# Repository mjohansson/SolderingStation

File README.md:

# SolderingStation
Project directory for soldering-station 2000

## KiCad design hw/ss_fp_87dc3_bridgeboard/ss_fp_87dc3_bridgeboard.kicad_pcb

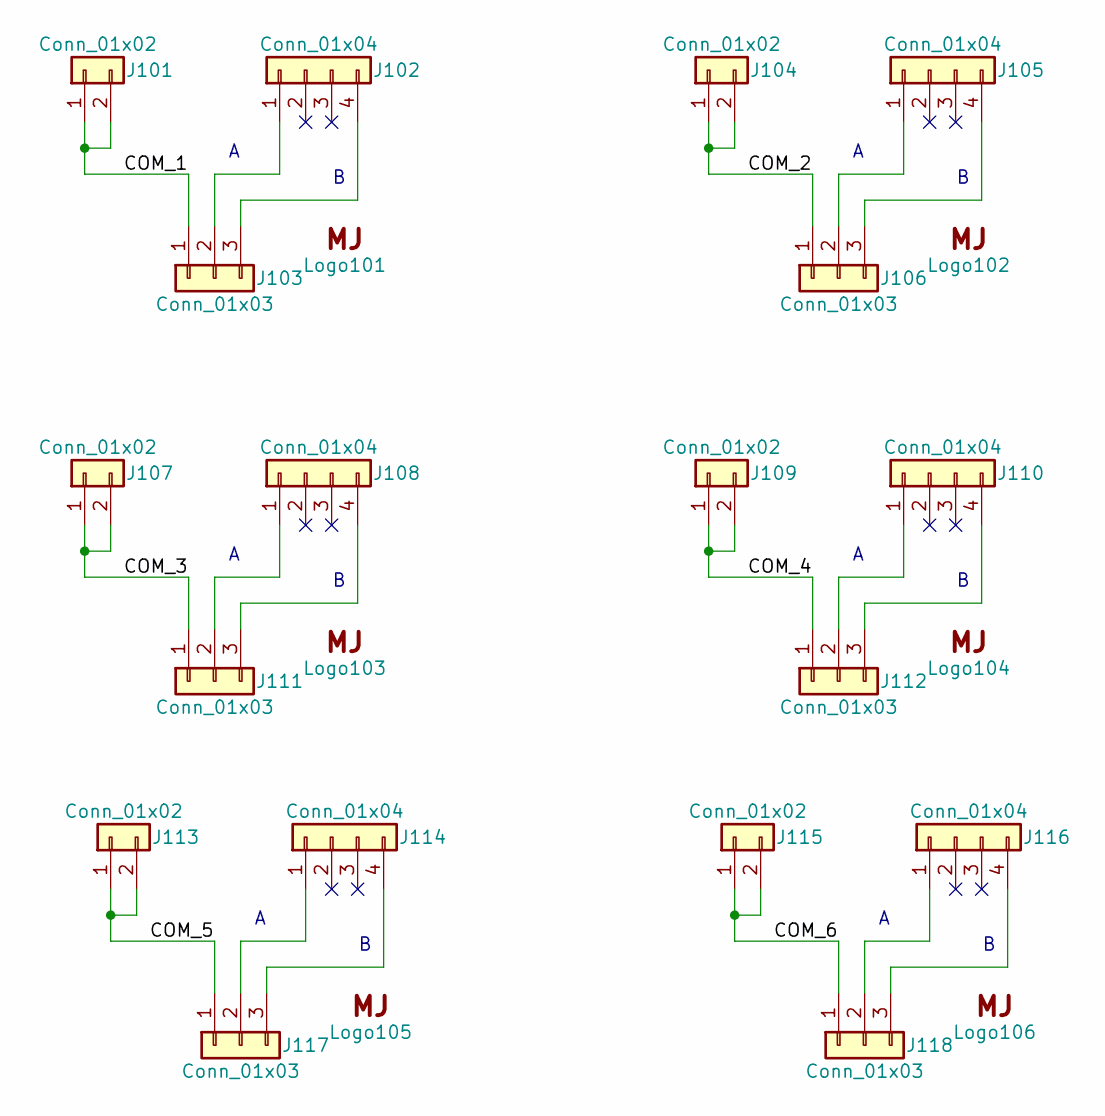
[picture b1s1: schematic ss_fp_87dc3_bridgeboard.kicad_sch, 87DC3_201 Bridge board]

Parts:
J101, J104, J107, J109, J113, J115: Conn_01x02; PinSocket_1x02_P2.54mm_Vertical
J102, J105, J108, J110, J114, J116: Conn_01x04; PinSocket_1x04_P2.54mm_Vertical
J103, J106, J111, J112, J117, J118: Conn_01x03; PinSocket_1x03_P2.54mm_Vertical
Logo101, Logo102, Logo103, Logo104, Logo105, Logo106: Logo_MJ; MJ_Mini

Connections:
/COM_1: J101.1, J101.2, J103.1
/COM_2: J104.1, J104.2, J106.1
/COM_3: J107.1, J107.2, J111.1
/COM_4: J109.1, J109.2, J112.1
/COM_5: J113.1, J113.2, J117.1
/COM_6: J115.1, J115.2, J118.1
unnamed: J102.1, J103.2
unnamed: J102.4, J103.3
unnamed: J105.1, J106.2
unnamed: J105.4, J106.3
unnamed: J108.1, J111.2
unnamed: J108.4, J111.3
unnamed: J110.1, J112.2
unnamed: J110.4, J112.3
unnamed: J114.1, J117.2
unnamed: J114.4, J117.3
unnamed: J116.1, J118.2
unnamed: J116.4, J118.3

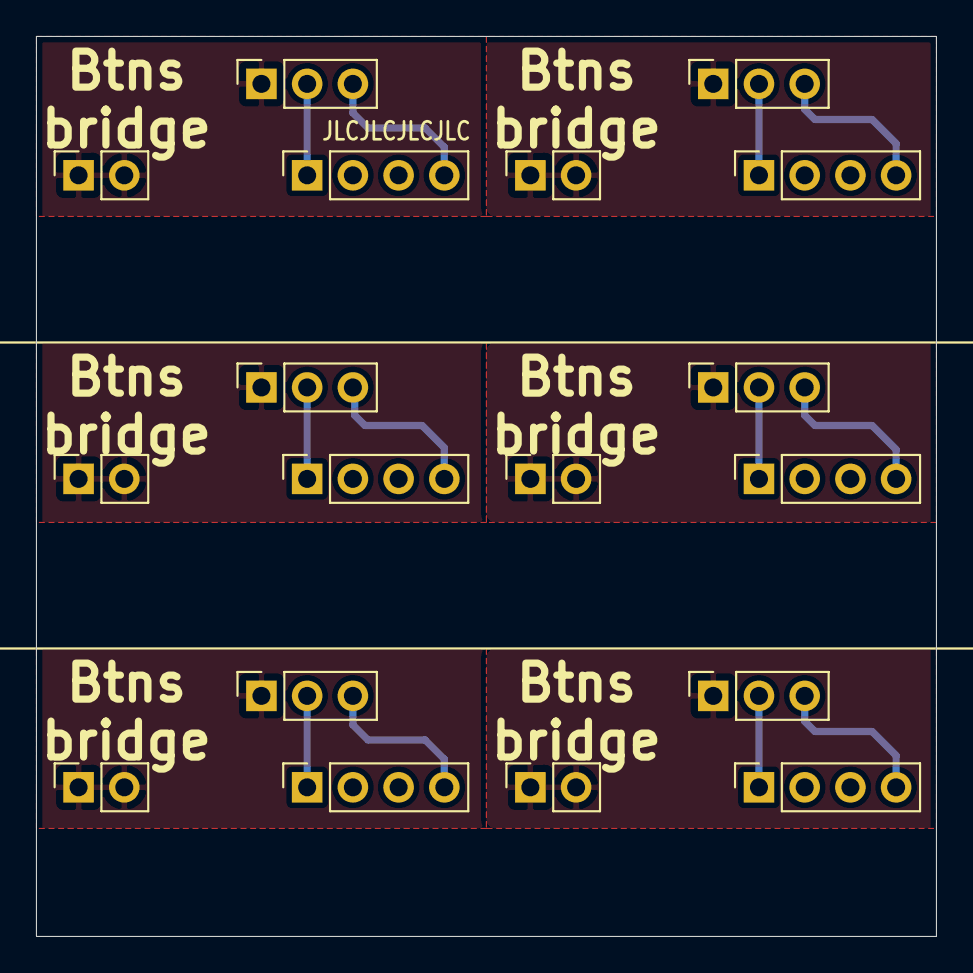
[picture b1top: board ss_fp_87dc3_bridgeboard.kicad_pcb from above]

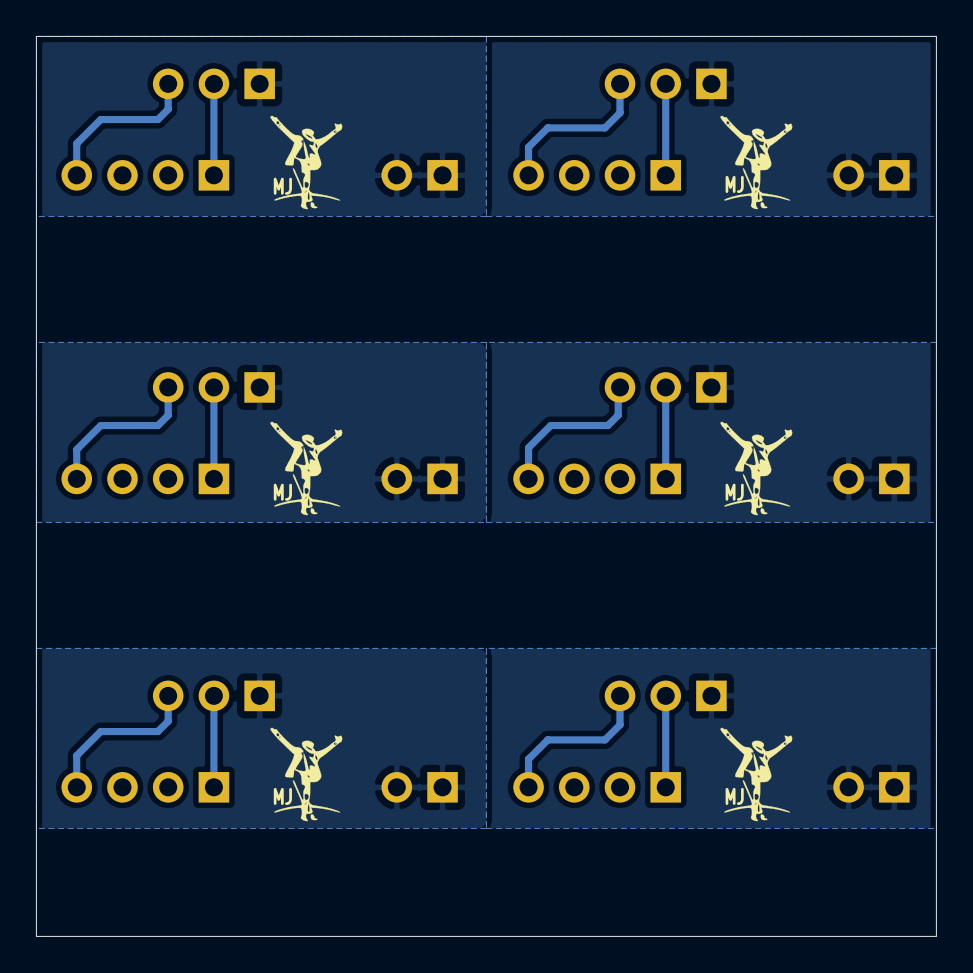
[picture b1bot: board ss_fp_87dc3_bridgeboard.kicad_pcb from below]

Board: 2 copper layers, 50.0 x 50.0 mm, 24 parts (6 on the bottom side), 18 nets.

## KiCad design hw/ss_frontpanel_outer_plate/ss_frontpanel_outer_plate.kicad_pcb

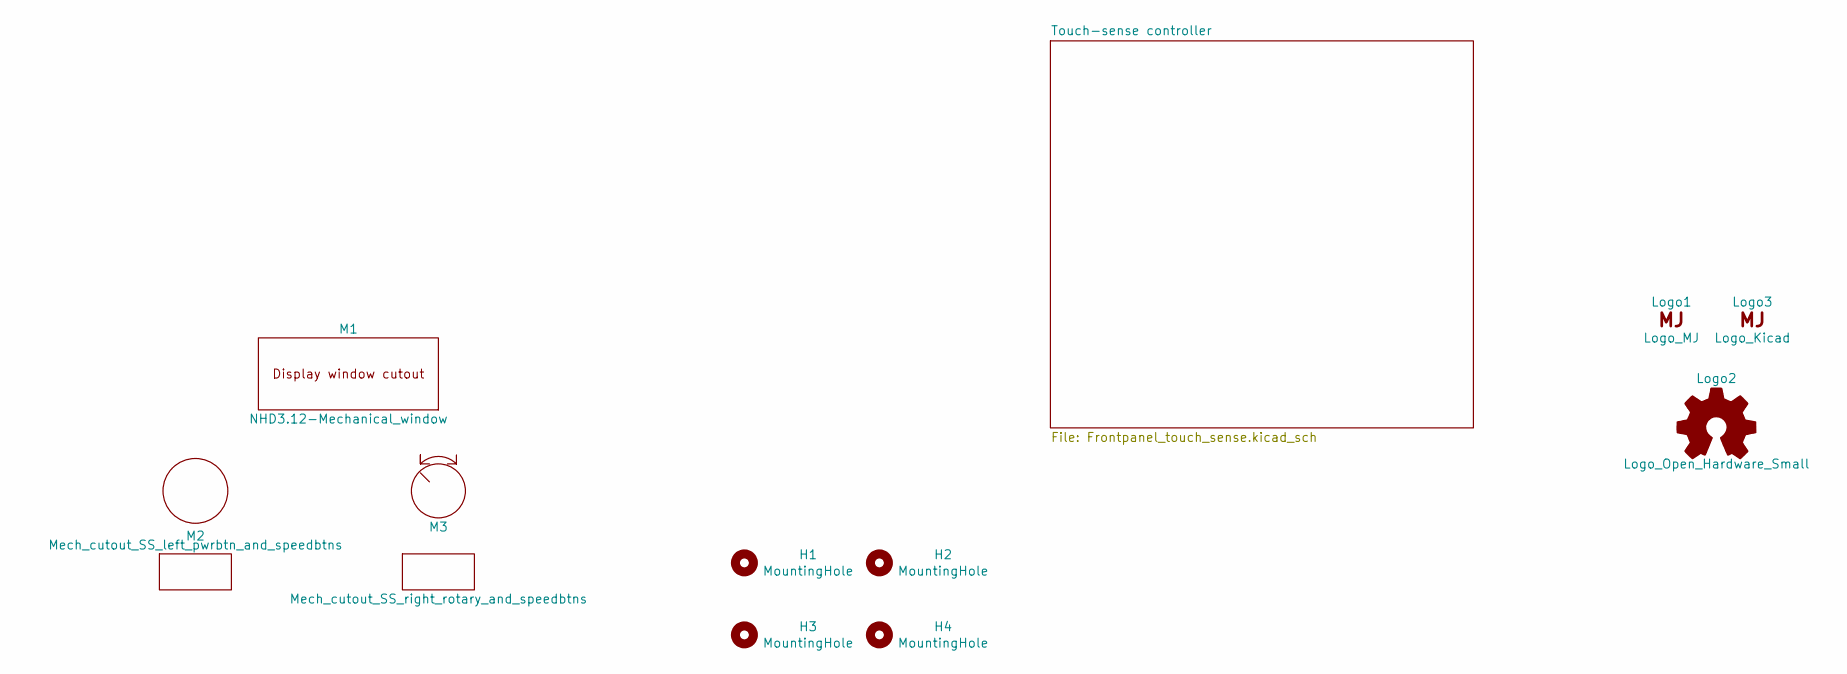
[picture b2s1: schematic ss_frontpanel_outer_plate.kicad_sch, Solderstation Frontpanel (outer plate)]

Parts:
H1, H2, H3, H4: MountingHole; MountingHole_3.5mm_Hammond_panel_screws
Logo1: Logo_MJ; MJ_10.3x12.7
Logo2: Logo_Open_Hardware_Small; OSHW-Logo_5.7x6mm_SilkScreen
Logo3: Logo_Kicad; KiCad-Logo2_5mm_SilkScreen
M1: NHD3.12-Mechanical_window; NHD3_12-Reverse_Bezel
M2: Mech_cutout_SS_left_pwrbtn_and_speedbtns; Frontpanel_L_Powerbtn_Pushbtns_outer_cutouts
M3: Mech_cutout_SS_right_rotary_and_speedbtns; Frontpanel_R_RotaryEnc_Pushbtns_outer_cutouts

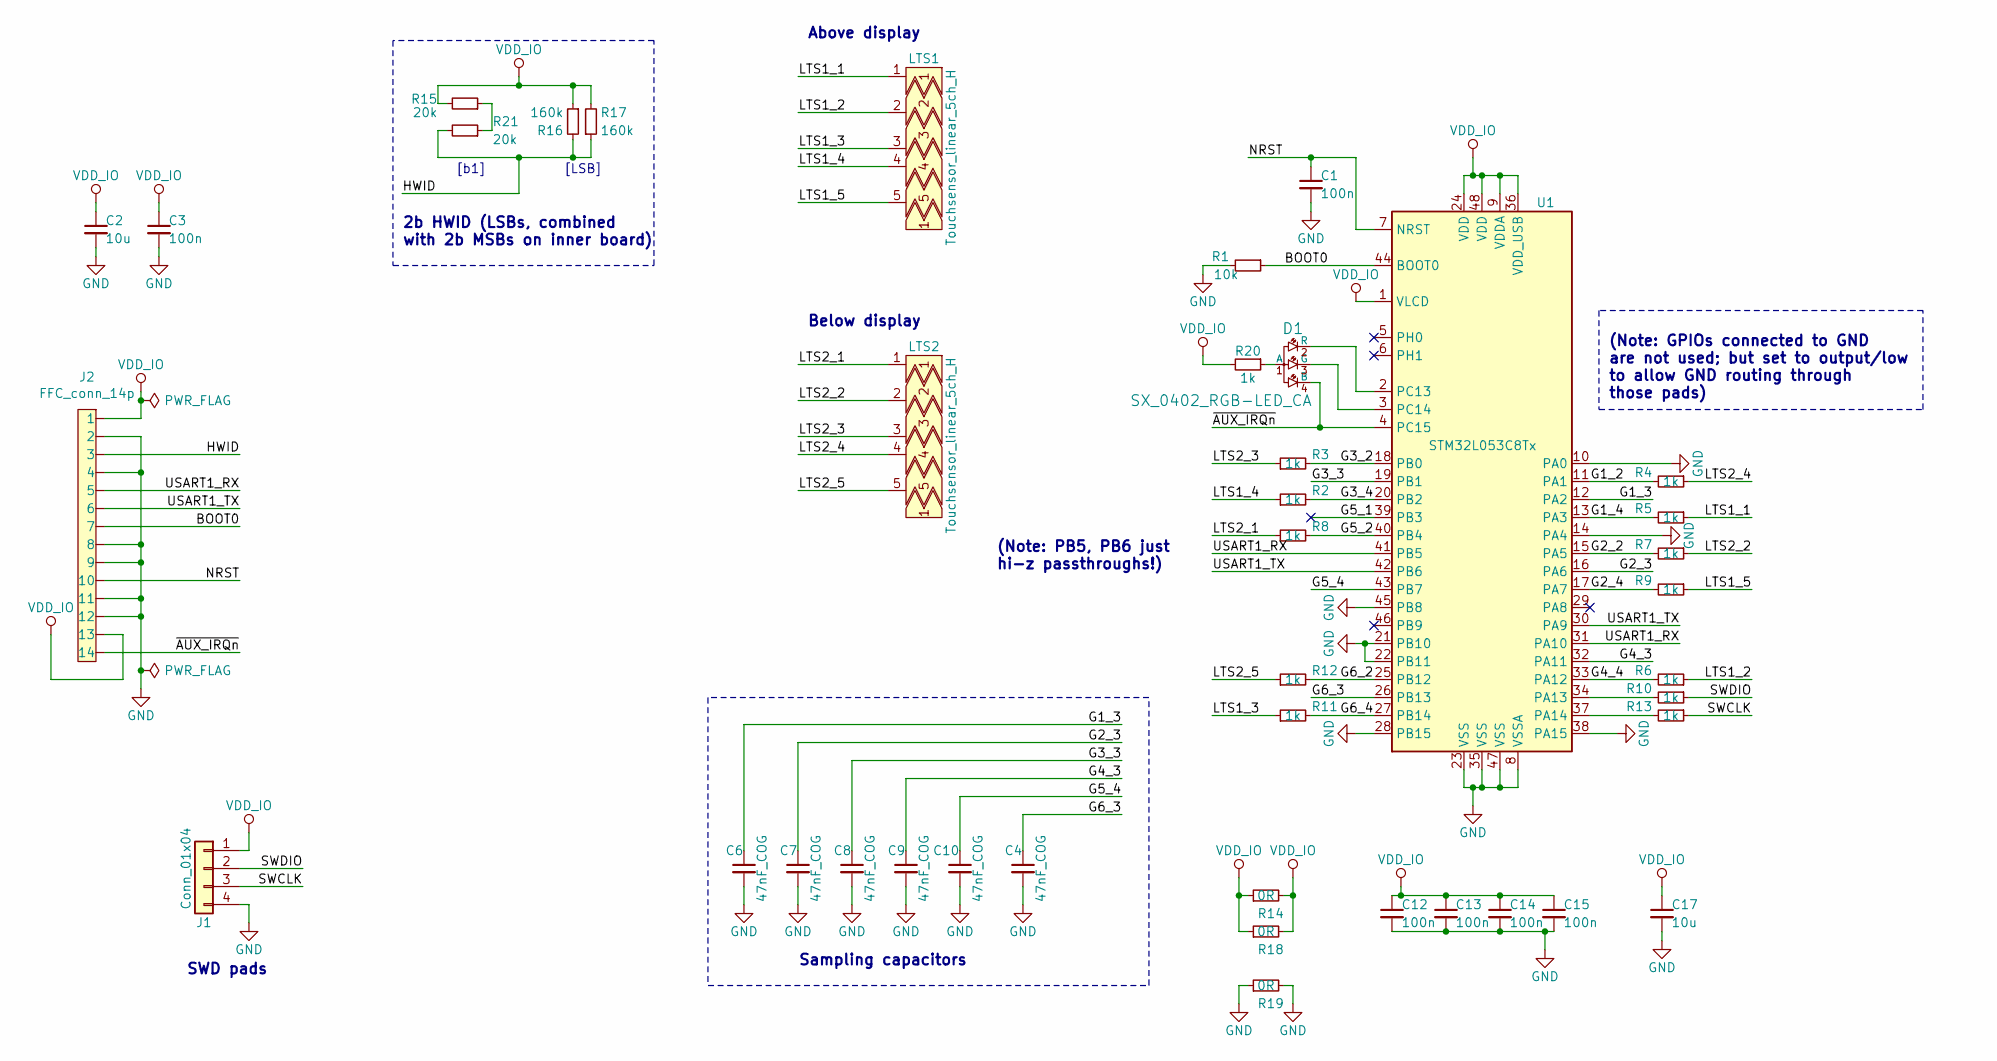
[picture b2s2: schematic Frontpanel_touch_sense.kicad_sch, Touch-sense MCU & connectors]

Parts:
C1, C3, C12, C13, C14, C15: 100n; C_0402_1005Metric
C2, C17: 10u; C_0402_1005Metric
C4, C6, C7, C8, C9, C10: 47nF_COG; C_1206_3216Metric
D1: SX_0402_RGB-LED_CA; SX_0402_RGB-CA-06
J1: Conn_01x04; 4pin_SWD_SMT_100mil
J2: FFC_conn_14p; FPC_14p_05mm-WE_687114182122
LTS1, LTS2: Touchsensor_linear_5ch_H; Touchsensor_linear_slider-5ch_H_90x8mm
R1: 10k; R_0402_1005Metric
R2, R3, R4, R5, R6, R7, R9, R10, R13, R20: 1k; R_0402_1005Metric
R8, R11: 1k; R_0603_1608Metric
R12: 1k; R_1206_3216Metric
R14, R18, R19: 0R; R_0603_1608Metric
R15, R21: 20k; R_0402_1005Metric
R16, R17: 160k; R_0402_1005Metric
U1: STM32L053C8Tx; LQFP-48_7x7mm_P0.5mm

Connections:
/Touch-sense controller/BOOT0: J2.7, R1.1, U1.44 (BOOT0)
/Touch-sense controller/G1_2: R4.2, U1.11 (PA1)
/Touch-sense controller/G1_3: C6.1, U1.12 (PA2)
/Touch-sense controller/G1_4: R5.2, U1.13 (PA3)
/Touch-sense controller/G2_2: R7.2, U1.15 (PA5)
/Touch-sense controller/G2_3: C7.1, U1.16 (PA6)
/Touch-sense controller/G2_4: R9.2, U1.17 (PA7)
/Touch-sense controller/G3_2: R3.2, U1.18 (PB0)
/Touch-sense controller/G3_3: C8.1, U1.19 (PB1)
/Touch-sense controller/G3_4: R2.2, U1.20 (PB2)
/Touch-sense controller/G4_3: C9.1, U1.32 (PA11)
/Touch-sense controller/G4_4: R6.2, U1.33 (PA12)
/Touch-sense controller/G5_1: U1.39 (PB3)
/Touch-sense controller/G5_2: R8.2, U1.40 (PB4)
/Touch-sense controller/G5_4: C10.1, U1.43 (PB7)
/Touch-sense controller/G6_2: R12.2, U1.25 (PB12)
/Touch-sense controller/G6_3: C4.1, U1.26 (PB13)
/Touch-sense controller/G6_4: R11.2, U1.27 (PB14)
/Touch-sense controller/HWID: J2.3, R16.2, R17.1, R21.2
/Touch-sense controller/LTS1_1: LTS1.1, R5.1
/Touch-sense controller/LTS1_2: LTS1.2, R6.1
/Touch-sense controller/LTS1_3: LTS1.3, R11.1
/Touch-sense controller/LTS1_4: LTS1.4, R2.1
/Touch-sense controller/LTS1_5: LTS1.5, R9.1
/Touch-sense controller/LTS2_1: LTS2.1, R8.1
/Touch-sense controller/LTS2_2: LTS2.2, R7.1
/Touch-sense controller/LTS2_3: LTS2.3, R3.1
/Touch-sense controller/LTS2_4: LTS2.4, R4.1
/Touch-sense controller/LTS2_5: LTS2.5, R12.1
/Touch-sense controller/NRST: C1.1, J2.10, U1.7 (NRST)
/Touch-sense controller/SWCLK: J1.3, R13.1
/Touch-sense controller/SWDIO: J1.2, R10.1
/Touch-sense controller/USART1_RX: J2.5, U1.31 (PA10), U1.41 (PB5)
/Touch-sense controller/USART1_TX: J2.6, U1.30 (PA9), U1.42 (PB6)
/Touch-sense controller/~AUX_IRQn: D1.4 (B), J2.14, U1.4 (PC15)
GND: C1.2, C2.2, C3.2, C4.2, C6.2, C7.2, C8.2, C9.2, C10.2, C12.2, C13.2, C14.2, C15.2, C17.2, J1.4, J2.2, J2.4, J2.8, J2.9, J2.11, J2.12, R1.2, R19.1, R19.2, U1.8 (VSSA), U1.10 (PA0), U1.14 (PA4), U1.21 (PB10), U1.22 (PB11), U1.23 (VSS), U1.28 (PB15), U1.35 (VSS), U1.38 (PA15), U1.45 (PB8), U1.47 (VSS)
unnamed: D1.1 (A), R20.1
unnamed: D1.2 (R), U1.2 (PC13)
unnamed: D1.3 (G), U1.3 (PC14)
unnamed: R10.2, U1.34 (PA13)
unnamed: R13.2, U1.37 (PA14)
unnamed: R15.1, R21.1
VDD_IO: C2.1, C3.1, C12.1, C13.1, C14.1, C15.1, C17.1, J1.1, J2.1, J2.13, R14.1, R14.2, R15.2, R16.1, R17.2, R18.1, R18.2, R20.2, U1.1 (VLCD), U1.9 (VDDA), U1.24 (VDD), U1.36 (VDD_USB), U1.48 (VDD)

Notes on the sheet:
(Note: PB5, PB6 just hi-z passthroughs!)
(Note: GPIOs connected to GND are not used; but set to output/low to allow GND routing through those pads)
SWD pads
[LSB]
Sampling capacitors
[b1]
Below display
2b HWID (LSBs, combined with 2b MSBs on inner board)
Above display

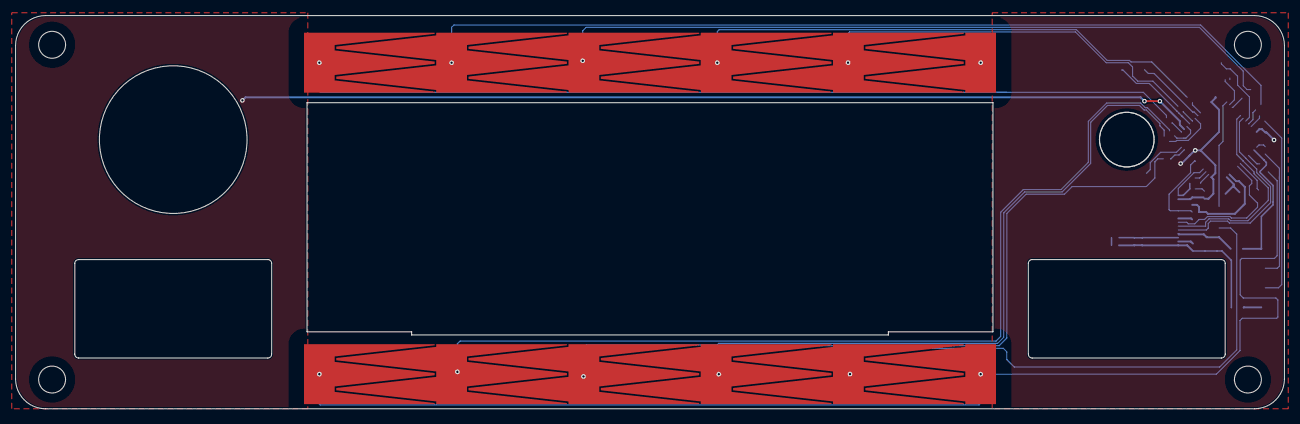
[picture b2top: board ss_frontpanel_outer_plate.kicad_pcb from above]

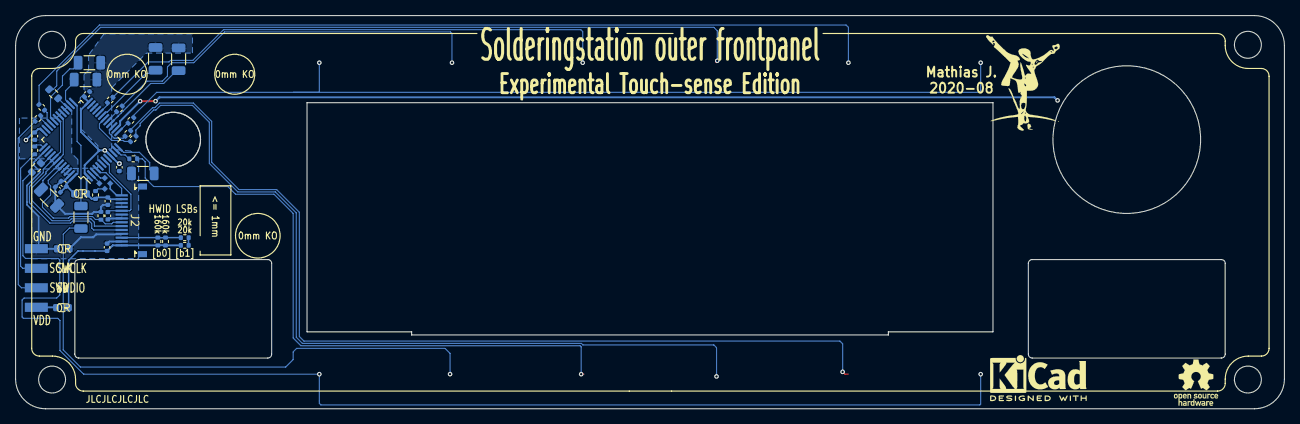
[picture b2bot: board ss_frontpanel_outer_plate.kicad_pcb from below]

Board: 2 copper layers, 165.0 x 51.1 mm, 51 parts (44 on the bottom side), 42 nets.

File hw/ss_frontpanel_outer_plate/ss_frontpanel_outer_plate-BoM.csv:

"Id";"Designator";"Package";"Quantity";"Designation";"Supplier and ref";
1;"H2,H3,H4,H1";"MountingHole_3.5mm_Hammond_panel_screws";4;"MountingHole";;;
2;"M1";"NHD3_12-Reverse_Bezel";1;"NHD3.12-Mechanical_window";;;
3;"LTS1,LTS2";"Touchsensor_linear_slider-5ch_H_90x8mm";2;"Touchsensor_linear_5ch_H";;;
4;"M2";"Frontpanel_L_Powerbtn_Pushbtns_outer_cutouts";1;"Mech_cutout_SS_left_pwrbtn_and_speedbtns";;;
5;"C1,C3,C12,C13,C15,C14";"C_0402_1005Metric";6;"100n";;;
6;"C6,C7,C8,C9,C4,C10";"C_1206_3216Metric";6;"47nF_COG";;;
7;"C17,C2";"C_0402_1005Metric";2;"10u";;;
8;"R1";"R_0402_1005Metric";1;"10k";;;
9;"R2,R6,R9,R5,R3,R4,R7,R10,R13,R20";"R_0402_1005Metric";10;"1k";;;
10;"R8,R11";"R_0603_1608Metric";2;"1k";;;
11;"R12";"R_1206_3216Metric";1;"1k";;;
12;"M3";"Frontpanel_R_RotaryEnc_Pushbtns_outer_cutouts";1;"Mech_cutout_SS_right_rotary_and_speedbtns";;;
13;"J2";"FPC_14p_05mm-WE_687114182122";1;"FFC_conn_14p";;;
14;"R17,R16";"R_0402_1005Metric";2;"160k";;;
15;"R18,R19,R14";"R_0603_1608Metric";3;"0R";;;
16;"J1";"4pin_SWD_SMT_100mil";1;"Conn_01x04";;;
17;"Logo1";"MJ_10.3x12.7";1;"Logo_MJ";;;
18;"Logo2";"OSHW-Logo_5.7x6mm_SilkScreen";1;"Logo_Open_Hardware_Small";;;
19;"Logo3";"KiCad-Logo2_5mm_SilkScreen";1;"Logo_Kicad";;;
20;"U1";"LQFP-48_7x7mm_P0.5mm";1;"STM32L052C8Tx";;;
21;"D1";"SX_0402_RGB-CA-06";1;"SX_0402_RGB-LED_CA";;;
22;"R15,R21";"R_0402_1005Metric";2;"20k";;;

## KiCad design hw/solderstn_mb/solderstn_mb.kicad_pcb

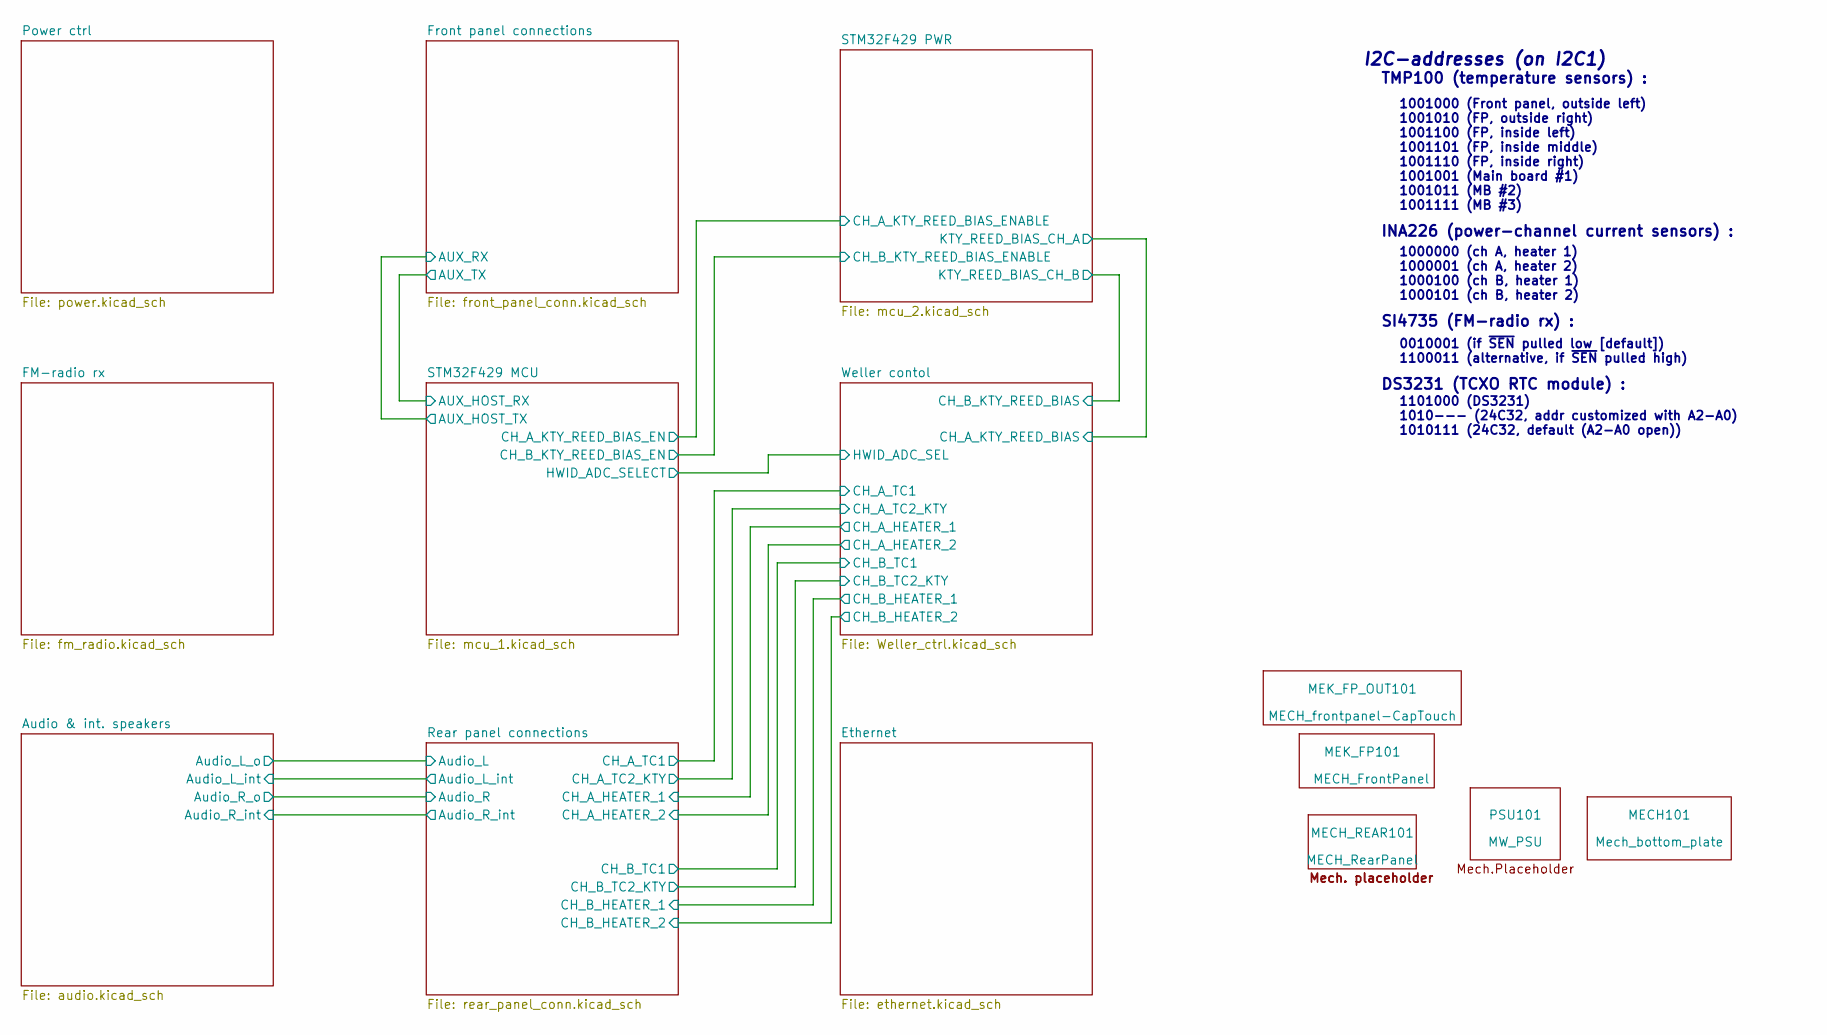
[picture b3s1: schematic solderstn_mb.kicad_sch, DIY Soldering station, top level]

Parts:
MECH101: Mech_bottom_plate; MECH_BTM_PLATE
MECH_REAR101: MECH_RearPanel; Mech_RearPanel
MEK_FP101: MECH_FrontPanel; Mech_frontpanel
MEK_FP_OUT101: MECH_frontpanel-CapTouch; Mech_Frontpanel_CapTouch
PSU101: MW_PSU

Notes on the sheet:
1000000 (ch A, heater 1) 1000001 (ch A, heater 2) 1000100 (ch B, heater 1) 1000101 (ch B, heater 2)
1001000 (Front panel, outside left) 1001010 (FP, outside right) 1001100 (FP, inside left) 1001101 (FP, inside middle) 1001110 (FP, inside right) 1001001 (Main board #1) 1001011 (MB #2) 1001111 (MB #3)
INA226 (power-channel current sensors) :
DS3231 (TCXO RTC module) :
I2C-addresses (on I2C1)
TMP100 (temperature sensors) :
1101000 (DS3231) 1010--- (24C32, addr customized with A2-A0) 1010111 (24C32, default (A2-A0 open))
SI4735 (FM-radio rx) :
0010001 (if ~{SEN} pulled low [default]) 1100011 (alternative, if ~{SEN} pulled high)

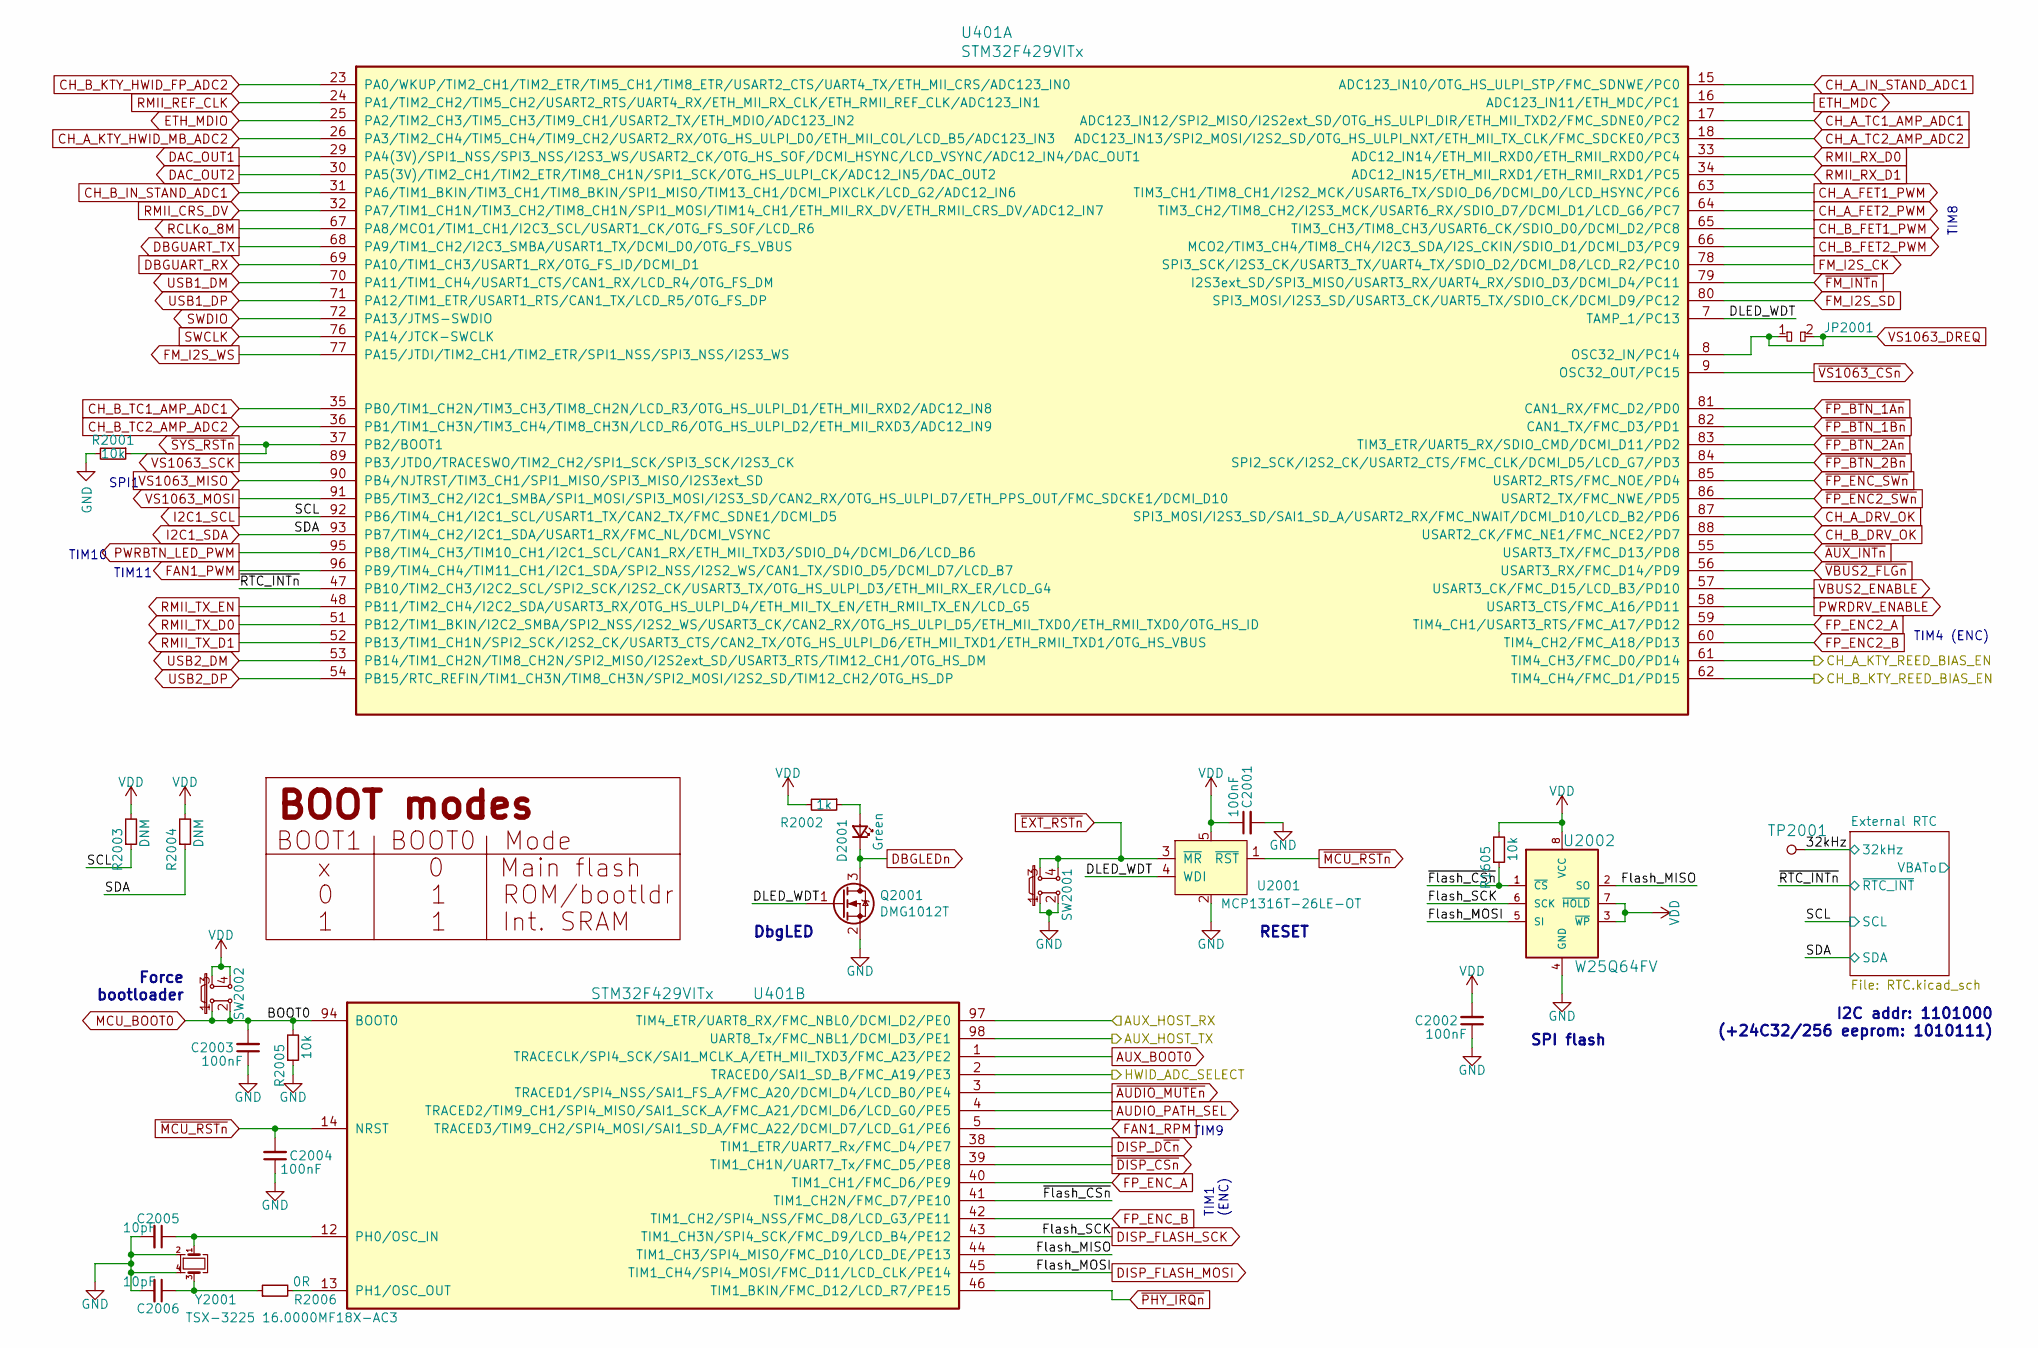
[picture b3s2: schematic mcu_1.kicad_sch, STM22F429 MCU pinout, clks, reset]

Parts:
C2001, C2002, C2003, C2004: 100nF; C_0402_1005Metric; JLC_part Basic
C2005, C2006: 10pF; C_0402_1005Metric; JLC_part Basic
D2001: Green; LED_0603_1608Metric; JLC_part Basic
JP2001: dogbone_2_ud; db2_ud_0402
Q2001: DMG1012T; SOT-523_handsoldering; JLC_part Extended
R1605, R2001, R2005: 10k; R_0402_1005Metric; JLC_part Basic
R2002: 1k; R_0402_1005Metric; JLC_part Basic
R2003, R2004: DNM; R_0402_1005Metric
R2006: 0R; R_0402_1005Metric; JLC_part Basic
SW2001, SW2002: Pushbutton_SMD_TS-1102W-4316; SMD_PUSHBTN_6x6mm
TP2001: TP; TP_SMD_1.2c
U401: STM32F429VITx; LQFP-100_14x14mm_P0.5mm; JLC_part Extended
U2001: MCP1316T-26LE-OT; SOT-23-5_HandSoldering
U2002: W25Q64FV; SOIC-8_5.275x5.275mm_P1.27mm; JLC_part Basic
Y2001: TSX-3225 16.0000MF18X-AC3; Crystal_SMD_SeikoEpson_TSX3225-4Pin_3.2x2.5mm; JLC_part Basic

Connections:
/Front panel connections/AUX_RX: U401.98 (UART8_Tx/FMC_NBL1/DCMI_D3/PE1); also elsewhere on the board
/Front panel connections/AUX_TX: U401.97 (TIM4_ETR/UART8_RX/FMC_NBL0/DCMI_D2/PE0); also elsewhere on the board
/STM32F429 MCU/32kHz: TP2001.1; also elsewhere on the board
/STM32F429 MCU/CH_A_KTY_REED_BIAS_EN: U401.61 (TIM4_CH3/FMC_D0/PD14); also elsewhere on the board
/STM32F429 MCU/CH_B_KTY_REED_BIAS_EN: U401.62 (TIM4_CH4/FMC_D1/PD15); also elsewhere on the board
/STM32F429 MCU/DLED_WDT: Q2001.1 (G), U401.7 (TAMP_1/PC13), U2001.4 (WDI)
/STM32F429 MCU/Flash_MISO: U401.44 (TIM1_CH3/SPI4_MISO/FMC_D10/LCD_DE/PE13), U2002.2 (SO)
/STM32F429 MCU/HWID_ADC_SELECT: U401.2 (TRACED0/SAI1_SD_B/FMC_A19/PE3); also elsewhere on the board
/STM32F429 MCU/~Flash_CSn: R1605.1, U401.41 (TIM1_CH2N/FMC_D7/PE10), U2002.1 (~CS)
/STM32F429 MCU/~RTC_INTn: U401.47 (PB10/TIM2_CH3/I2C2_SCL/SPI2_SCK/I2S2_CK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); also elsewhere on the board
AGND: C2001.2, C2002.1, C2003.1, C2004.1, C2005.2, C2006.2, Q2001.2 (S), R2001.2, R2005.1, SW2001.1, SW2001.2, U2001.2, U2002.4 (GND), Y2001.2, Y2001.4; also elsewhere on the board
AUDIO_PATH_SEL: U401.4 (TRACED2/TIM9_CH1/SPI4_MISO/SAI1_SCK_A/F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); also elsewhere on the board
AUX_BOOT0: U401.1 (TRACECLK/SPI4_SCK/SAI1_MCLK_A/ETH_MII_T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); also elsewhere on the board
CH_A_DRV_OK: U401.87 (SPI3_MOSI/I2S3_SD/SAI1_SD_A/USART2_RX/F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); also elsewhere on the board
CH_A_FET1_PWM: U401.63 (TIM3_CH1/TIM8_CH1/I2S2_MCK/USART6_TX/SD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); also elsewhere on the board
CH_A_FET2_PWM: U401.64 (TIM3_CH2/TIM8_CH2/I2S3_MCK/USART6_RX/SD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); also elsewhere on the board
CH_A_IN_STAND_ADC1: U401.15 (ADC123_IN10/OTG_HS_ULPI_STP/FMC_SDNWE/P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); also elsewhere on the board
CH_A_KTY_HWID_MB_ADC2: U401.26 (PA3/TIM2_CH4/TIM5_CH4/TIM9_CH2/USART2_R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); also elsewhere on the board
CH_A_TC1_AMP_ADC1: U401.17 (ADC123_IN12/SPI2_MISO/I2S2ext_SD/OTG_HS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); also elsewhere on the board
CH_A_TC2_AMP_ADC2: U401.18 (ADC123_IN13/SPI2_MOSI/I2S2_SD/OTG_HS_UL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); also elsewhere on the board
CH_B_DRV_OK: U401.88 (USART2_CK/FMC_NE1/FMC_NCE2/PD7); also elsewhere on the board
CH_B_FET1_PWM: U401.65 (TIM3_CH3/TIM8_CH3/USART6_CK/SDIO_D0/DCM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); also elsewhere on the board
CH_B_FET2_PWM: U401.66 (MCO2/TIM3_CH4/TIM8_CH4/I2C3_SDA/I2S_CKI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); also elsewhere on the board
CH_B_IN_STAND_ADC1: U401.31 (PA6/TIM1_BKIN/TIM3_CH1/TIM8_BKIN/SPI1_M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); also elsewhere on the board
CH_B_KTY_HWID_FP_ADC2: U401.23 (PA0/WKUP/TIM2_CH1/TIM2_ETR/TIM5_CH1/TIM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); also elsewhere on the board
CH_B_TC1_AMP_ADC1: U401.35 (PB0/TIM1_CH2N/TIM3_CH3/TIM8_CH2N/LCD_R3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); also elsewhere on the board
CH_B_TC2_AMP_ADC2: U401.36 (PB1/TIM1_CH3N/TIM3_CH4/TIM8_CH3N/LCD_R6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); also elsewhere on the board
DAC_OUT1: U401.29 (PA4(3V)/SPI1_NSS/SPI3_NSS/I2S3_WS/USART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); also elsewhere on the board
DAC_OUT2: U401.30 (PA5(3V)/TIM2_CH1/TIM2_ETR/TIM8_CH1N/SPI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); also elsewhere on the board
DBGLEDn: D2001.1 (K), Q2001.3 (D); also elsewhere on the board
DBGUART_RX: U401.69 (PA10/TIM1_CH3/USART1_RX/OTG_FS_ID/DCMI_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); also elsewhere on the board
DBGUART_TX: U401.68 (PA9/TIM1_CH2/I2C3_SMBA/USART1_TX/DCMI_D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); also elsewhere on the board
DISP_D~Cn: U401.38 (TIM1_ETR/UART7_Rx/FMC_D4/PE7); also elsewhere on the board
DISP_FLASH_MOSI: U401.45 (TIM1_CH4/SPI4_MOSI/FMC_D11/LCD_CLK/PE14), U2002.5 (SI); also elsewhere on the board
DISP_FLASH_SCK: U401.43 (TIM1_CH3N/SPI4_SCK/FMC_D9/LCD_B4/PE12), U2002.6 (SCK); also elsewhere on the board
ETH_MDC: U401.16 (ADC123_IN11/ETH_MDC/PC1); also elsewhere on the board
ETH_MDIO: U401.25 (PA2/TIM2_CH3/TIM5_CH3/TIM9_CH1/USART2_T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); also elsewhere on the board
FAN1_PWM: U401.96 (PB9/TIM4_CH4/TIM11_CH1/I2C1_SDA/SPI2_NS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); also elsewhere on the board
FAN1_RPM: U401.5 (TRACED3/TIM9_CH2/SPI4_MOSI/SAI1_SD_A/FM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); also elsewhere on the board
FM_I2S_CK: U401.78 (SPI3_SCK/I2S3_CK/USART3_TX/UART4_TX/SDI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); also elsewhere on the board
FM_I2S_SD: U401.80 (SPI3_MOSI/I2S3_SD/USART3_CK/UART5_TX/SD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); also elsewhere on the board
FM_I2S_WS: U401.77 (PA15/JTDI/TIM2_CH1/TIM2_ETR/SPI1_NSS/SP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); also elsewhere on the board
FP_ENC2_A: U401.59 (TIM4_CH1/USART3_RTS/FMC_A17/PD12); also elsewhere on the board
FP_ENC2_B: U401.60 (TIM4_CH2/FMC_A18/PD13); also elsewhere on the board
FP_ENC_A: U401.40 (TIM1_CH1/FMC_D6/PE9); also elsewhere on the board
FP_ENC_B: U401.42 (TIM1_CH2/SPI4_NSS/FMC_D8/LCD_G3/PE11); also elsewhere on the board
I2C1_SCL: R2003.1, U401.92 (PB6/TIM4_CH1/I2C1_SCL/USART1_TX/CAN2_TX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); also elsewhere on the board
I2C1_SDA: R2004.1, U401.93 (PB7/TIM4_CH2/I2C1_SDA/USART1_RX/FMC_NL/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); also elsewhere on the board
MCU_BOOT0: C2003.2, R2005.2, SW2002.1, SW2002.2, U401.94 (BOOT0); also elsewhere on the board
unnamed: C2005.1, U401.12 (PH0/OSC_IN), Y2001.1
unnamed: C2006.1, R2006.1, Y2001.3
unnamed: D2001.2 (A), R2002.1
unnamed: R2006.2, U401.13 (PH1/OSC_OUT)
PWRBTN_LED_PWM: U401.95 (PB8/TIM4_CH3/TIM10_CH1/I2C1_SCL/CAN1_RX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); also elsewhere on the board
PWRDRV_ENABLE: U401.58 (USART3_CTS/FMC_A16/PD11); also elsewhere on the board
RCLKo_8M: U401.67 (PA8/MCO1/TIM1_CH1/I2C3_SCL/USART1_CK/OT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); also elsewhere on the board
RMII_CRS_DV: U401.32 (PA7/TIM1_CH1N/TIM3_CH2/TIM8_CH1N/SPI1_M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); also elsewhere on the board
RMII_REF_CLK: U401.24 (PA1/TIM2_CH2/TIM5_CH2/USART2_RTS/UART4_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); also elsewhere on the board
RMII_RX_D0: U401.33 (ADC12_IN14/ETH_MII_RXD0/ETH_RMII_RXD0/P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); also elsewhere on the board
RMII_RX_D1: U401.34 (ADC12_IN15/ETH_MII_RXD1/ETH_RMII_RXD1/P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); also elsewhere on the board
RMII_TX_D0: U401.51 (PB12/TIM1_BKIN/I2C2_SMBA/SPI2_NSS/I2S2_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); also elsewhere on the board
RMII_TX_D1: U401.52 (PB13/TIM1_CH1N/SPI2_SCK/I2S2_CK/USART3_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); also elsewhere on the board
RMII_TX_EN: U401.48 (PB11/TIM2_CH4/I2C2_SDA/USART3_RX/OTG_HS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); also elsewhere on the board
SWCLK: U401.76 (PA14/JTCK-SWCLK); also elsewhere on the board
SWDIO: U401.72 (PA13/JTMS-SWDIO); also elsewhere on the board
USB1_DM: U401.70 (PA11/TIM1_CH4/USART1_CTS/CAN1_RX/LCD_R4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); also elsewhere on the board
USB1_DP: U401.71 (PA12/TIM1_ETR/USART1_RTS/CAN1_TX/LCD_R5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); also elsewhere on the board
USB2_DM: U401.53 (PB14/TIM1_CH2N/TIM8_CH2N/SPI2_MISO/I2S2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); also elsewhere on the board
USB2_DP: U401.54 (PB15/RTC_REFIN/TIM1_CH3N/TIM8_CH3N/SPI2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); also elsewhere on the board
VBUS2_ENABLE: U401.57 (USART3_CK/FMC_D15/LCD_B3/PD10); also elsewhere on the board
VCC: C2001.1, C2002.2, R1605.2, R2002.2, R2003.2, R2004.2, SW2002.3, SW2002.4, U2001.5, U2002.3 (~WP), U2002.7 (~HOLD), U2002.8 (VCC); also elsewhere on the board
VS1063_DREQ: JP2001.1, JP2001.2, U401.8 (OSC32_IN/PC14); also elsewhere on the board
VS1063_MISO: U401.90 (PB4/NJTRST/TIM3_CH1/SPI1_MISO/SPI3_MISO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); also elsewhere on the board
VS1063_MOSI: U401.91 (PB5/TIM3_CH2/I2C1_SMBA/SPI1_MOSI/SPI3_M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); also elsewhere on the board
VS1063_SCK: U401.89 (PB3/JTDO/TRACESWO/TIM2_CH2/SPI1_SCK/SPI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); also elsewhere on the board
~AUDIO_MUTEn: U401.3 (TRACED1/SPI4_NSS/SAI1_FS_A/FMC_A20/DCMI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); also elsewhere on the board
~AUX_INTn: U401.55 (USART3_TX/FMC_D13/PD8); also elsewhere on the board
~DISP_CSn: U401.39 (TIM1_CH1N/UART7_Tx/FMC_D5/PE8); also elsewhere on the board
~EXT_RSTn: SW2001.3, SW2001.4, U2001.3 (~MR); also elsewhere on the board
~FM_INTn: U401.79 (I2S3ext_SD/SPI3_MISO/USART3_RX/UART4_RX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); also elsewhere on the board
~FP_BTN_1An: U401.81 (CAN1_RX/FMC_D2/PD0); also elsewhere on the board
~FP_BTN_1Bn: U401.82 (CAN1_TX/FMC_D3/PD1); also elsewhere on the board
~FP_BTN_2An: U401.83 (TIM3_ETR/UART5_RX/SDIO_CMD/DCMI_D11/PD2); also elsewhere on the board
~FP_BTN_2Bn: U401.84 (SPI2_SCK/I2S2_CK/USART2_CTS/FMC_CLK/DCM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); also elsewhere on the board
~FP_ENC2_SWn: U401.86 (USART2_TX/FMC_NWE/PD5); also elsewhere on the board
~FP_ENC_SWn: U401.85 (USART2_RTS/FMC_NOE/PD4); also elsewhere on the board
~MCU_RSTn: C2004.2, U401.14 (NRST), U2001.1 (~RST); also elsewhere on the board
~PHY_IRQn: U401.46 (TIM1_BKIN/FMC_D12/LCD_R7/PE15); also elsewhere on the board
~SYS_RSTn: R2001.1, U401.37 (PB2/BOOT1); also elsewhere on the board
~VBUS2_FLGn: U401.56 (USART3_RX/FMC_D14/PD9); also elsewhere on the board
~VS1063_CSn: U401.9 (OSC32_OUT/PC15); also elsewhere on the board

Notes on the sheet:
TIM11
RESET
Force bootloader
SPI flash
TIM9
DbgLED
TIM10
SPI1
TIM1 (ENC)
I2C addr: 1101000 (+24C32/256 eeprom: 1010111)
TIM4 (ENC)
TIM8
